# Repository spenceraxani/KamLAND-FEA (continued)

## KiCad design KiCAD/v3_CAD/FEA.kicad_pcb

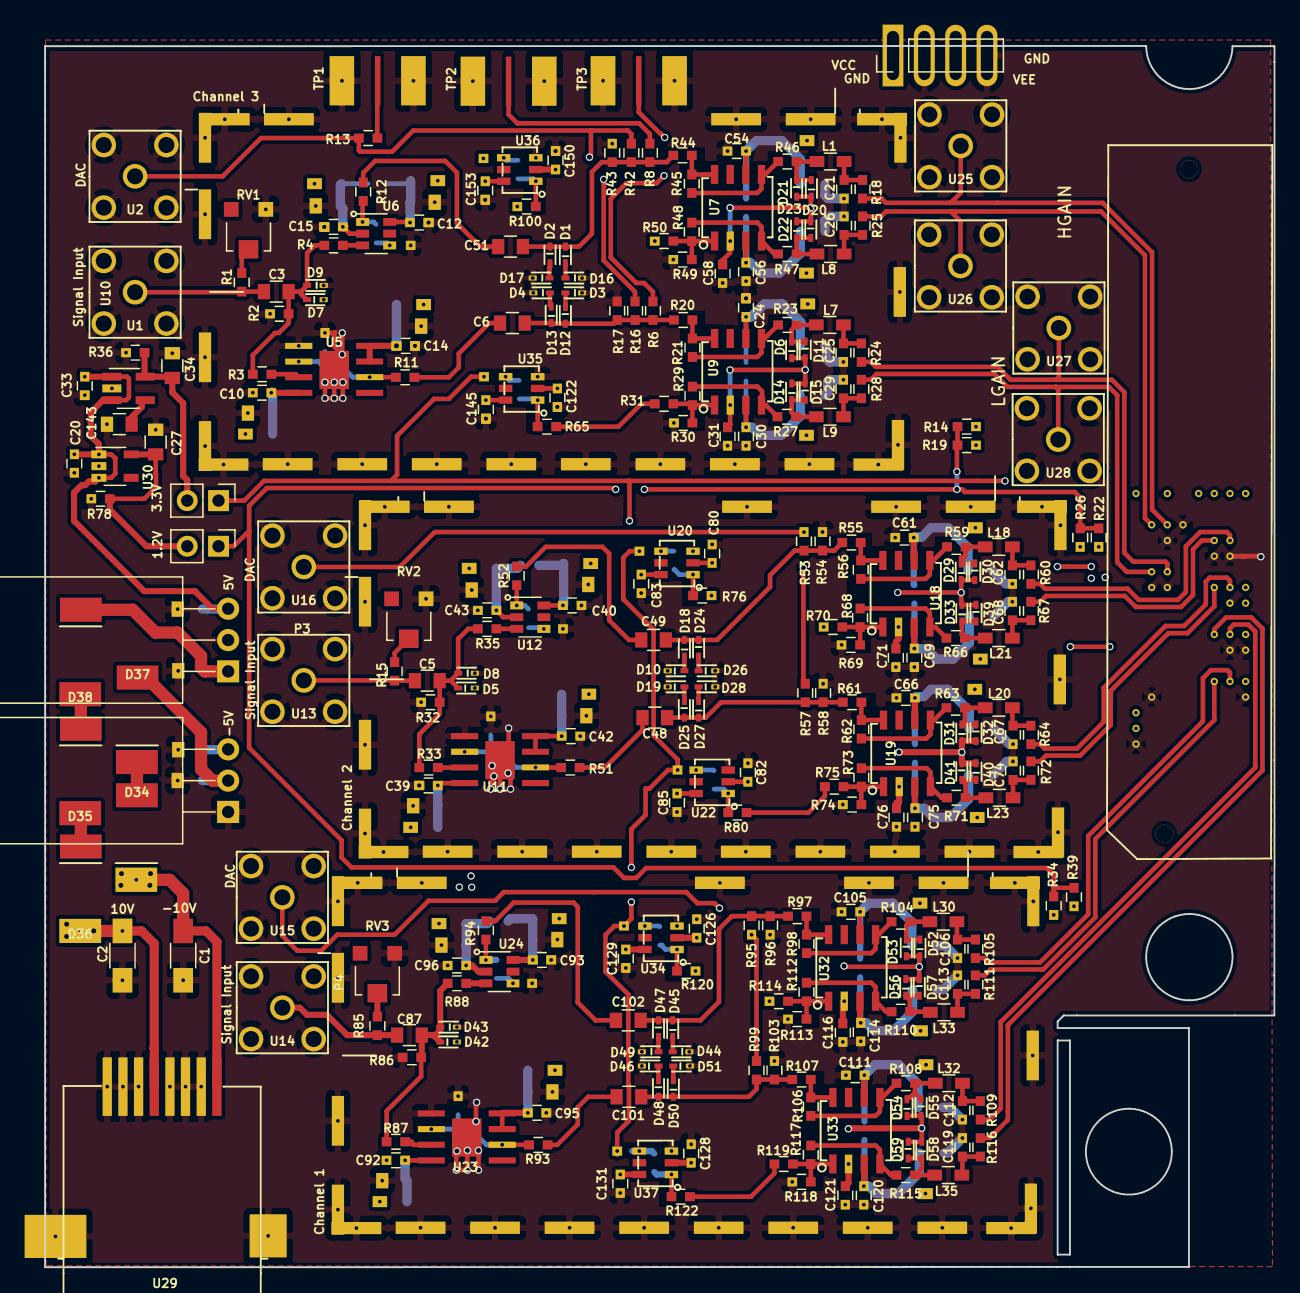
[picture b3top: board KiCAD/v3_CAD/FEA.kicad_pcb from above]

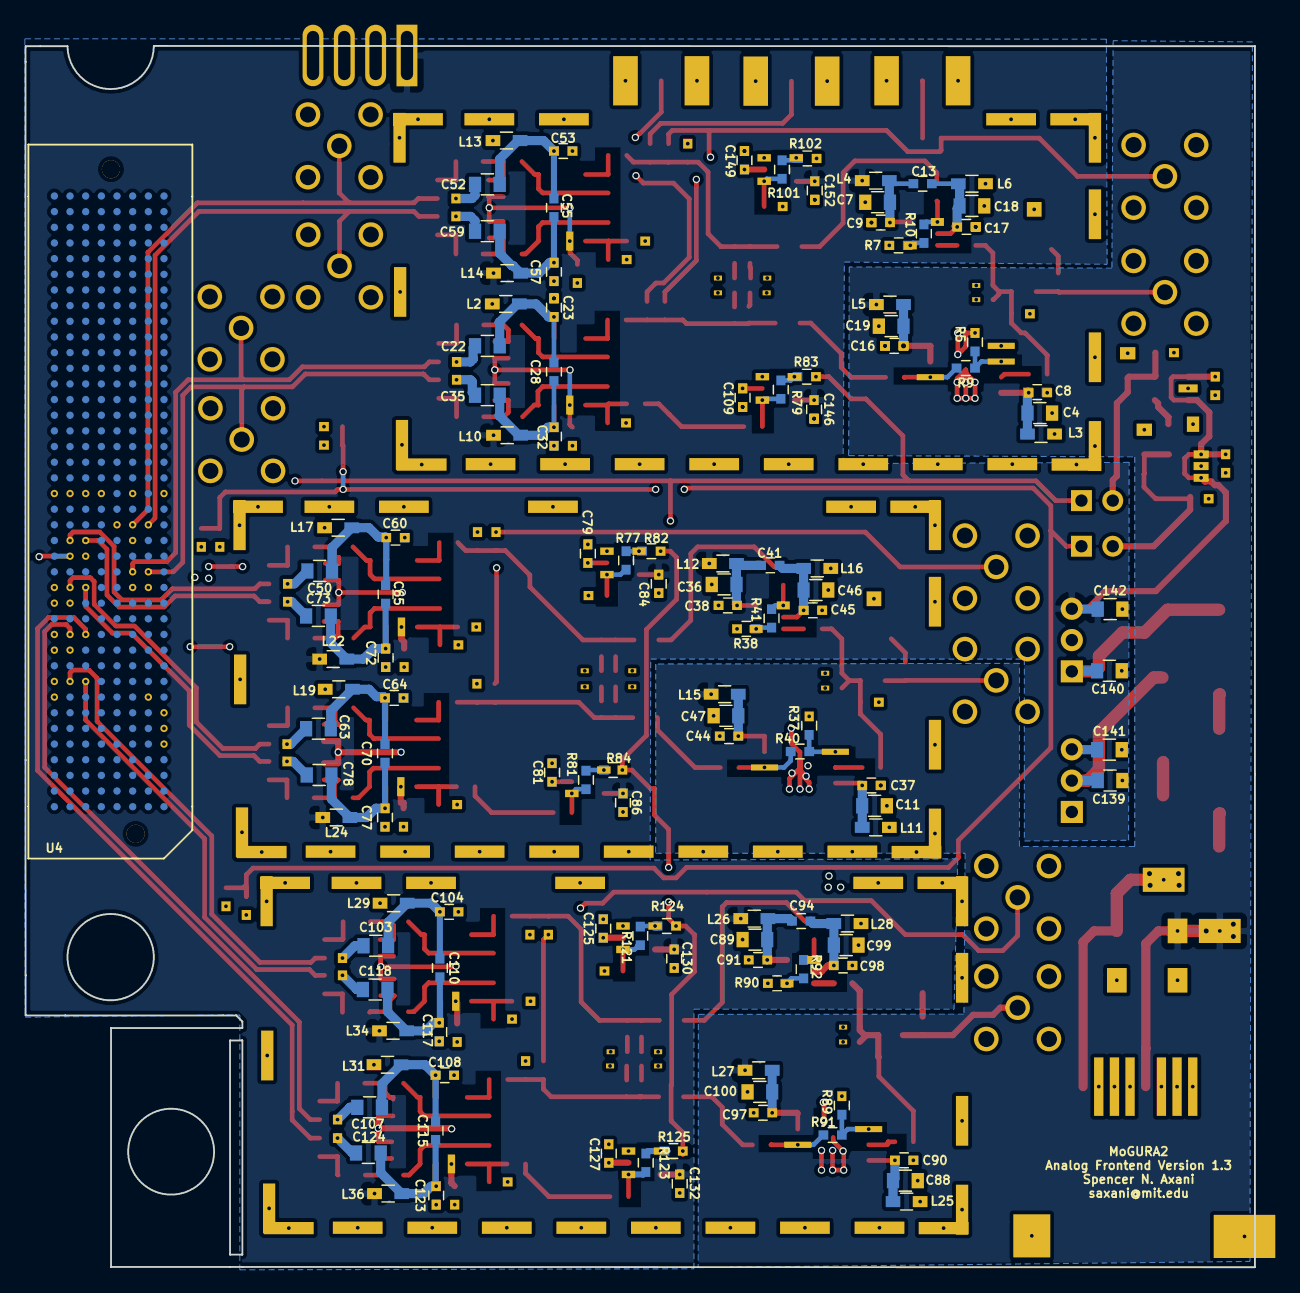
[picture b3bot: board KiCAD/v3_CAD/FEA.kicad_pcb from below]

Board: 4 copper layers, 99.7 x 99.1 mm, 409 parts (122 on the bottom side), 180 nets.

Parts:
C1, C2: CP1; C_1206_HandSoldering
C3, C5, C87: 0; C_0805
C4, C7, C11, C18, C19, C22, C35, C36, C46, C47, C50, C52, C59, C63, C73, C78, C88, C89, C99, C100, C103, C107, C118, C124: 10uF; C_0805
C6, C48, C49, C51, C101, C102: 22u; C_0805
C8, C9, C13, C16, C17, C21, C23, C25, C26, C28, C29, C31, C32, C37, C38, C41, C44, C45, C53, C55, C57, C58, C60, C62, C64, C65, C67, C68, C70, C71, C72, C74, C76, C77, C79, C81, C84, C86, C90, C91, C94, C97, C98, C104, C106, C108, C109, C110, C112, C113, C115, C116, C117, C119, C121, C123, C125, C127, C130, C132, C146, C149, C153: 0.1uF; C_0603
C10, C14, C39, C42, C92, C95: 100pF; C_0603
C12, C15, C24, C30, C40, C43, C54, C56, C61, C66, C69, C75, C80, C82, C83, C85, C93, C96, C105, C111, C114, C120, C122, C126, C128, C129, C131, C145, C150, C152: 10nF; C_0603
C20, C33: 1uF; C_0603
C27: 1u; C_0805
C34: 2.2u; C_0805
C139: 0.47u; C_0805
C140: 0.33uF; C_0805
C141: 2.2uF; C_0805
C142: 0.1uF; C_0805
C143: 1uF; C_0805
D1, D2, D3, D4, D5, D6, D7, D8, D9, D10, D11, D12, D13, D14, D15, D16, D17, D18, D19, D20, D21, D22, D23, D24, D25, D26, D27, D28, D29, D30, D31, D32, D33, D39, D40, D41, D42, D43, D44, D45, D46, D47, D48, D49, D50, D51, D52, D53, D54, D55, D56, D57, D58, D59: D; RB751
D34, D35, D36, D37, D38: D; SA3-Diode
JP8, JP10: Jumper_NC_Small; Pin_Header_Straight_1x02_Pitch2.54mm
L1, L2, L3, L4, L5, L6, L7, L8, L9, L10, L11, L12, L13, L14, L15, L16, L17, L18, L19, L20, L21, L22, L23, L24, L25, L26, L27, L28, L29, L30, L31, L32, L33, L34, L35, L36: BLM18BB221SN1; R_0603_HandSoldering
P1: CONN_01X04; Pin_Header_Straight_1x04_Pitch2.54mm
P2, P3, P4: CONN_01X01; RF SHIELD 1.094 X 2.23 SMD
R1, R15, R85: 100k; C_0603
R2, R3, R4, R12, R32, R33, R35, R52, R65, R76, R80, R86, R87, R88, R94, R100, R120, R122: 49.9; C_0603
R5, R9, R37, R40, R89, R91: 2.1k; C_0603
R6, R8, R13, R14, R19, R22, R26, R34, R39: R; C_0603
R7, R38, R90: 100; C_0603
R10, R41, R92: 390; C_0603
R11, R21, R29, R45, R48, R51, R56, R62, R68, R73, R93, R98, R107, R112, R117: 200; C_0603
R16, R17, R42, R43, R53, R54, R57, R58, R95, R96, R99, R103: 500; C_0603
R18, R23, R24, R25, R27, R28, R46, R47, R59, R60, R63, R64, R66, R67, R71, R72, R104, R105, R108, R109, R110, R111, R115, R116: 40; C_0603
R20, R44, R55, R61, R97, R106: 120; C_0603
R30, R49, R69, R74, R113, R118: 170; C_0603
R31, R50, R70, R75, R114, R119: 1.5k; C_0603
R36, R78: 10k; C_0603
R77, R79, R81, R82, R83, R84, R101, R102, R121, R123, R124, R125: 560; C_0603
RV1, RV2, RV3: POT; Potentiometer_Trimmer-EVM3E
U1, U2, U13, U14, U15, U16, U25, U26, U27, U28: SMA; SMA_90
U3, U8, U31: SMA; SMA_side_mount
U4: LPAM
U5, U11, U23: THS3491; THS3491_HSOIC
U6, U12, U24: LMH6703; SOT-23-6
U7, U9, U18, U19, U32, U33: LMH6552; LMH6550
U10: TPS7993; SOT-23-5_HandSoldering
U17: UA7905CKCSE3_-5V; TO-220_Horizontal
U20, U22, U34, U35, U36, U37: LMH6702MF; LMH6702
U21: L78S_5V; TO-220_Horizontal
U29: Ethernet; Ethernet_90_8P8C
U30: 5-Lead_TSOT; TSOT-23-5

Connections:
1.2V: JP10.1, R14.1, R19.1, R22.1, R26.1, R34.1, R39.1
5V: C20.1, C33.1, C83.2, C84.2, C85.2, C86.2, C129.2, C130.2, C131.2, C132.2, C142.1, C145.2, C146.2, C152.2, C153.2, L4.2, L10.1, L12.2, L14.1, L22.1, L24.1, L26.2, L34.1, L36.1, P1.1, U10.1, U10.3, U20.6, U21.3, U22.6, U30.1, U30.3, U34.6, U35.6, U36.6, U37.6
10V: C2.2, D36.2, L5.2, L15.2, L27.2, U29.4
-5V: C79.2, C80.2, C81.2, C82.2, C109.2, C122.2, C125.2, C126.2, C127.2, C128.2, C141.1, C149.2, C150.2, L2.2, L6.1, L13.2, L16.1, L17.2, L19.2, L28.1, L29.2, L31.2, P1.3, U17.3, U20.2, U22.2, U34.2, U35.2, U36.2, U37.2
-10V: C1.1, D5.2, D7.2, D34.1, D42.2, L3.1, L11.1, L25.1, U29.8
/Amp1/DAC_input: R13.1, R16.1, R42.1, U2.1
/Amp1/HGain_Bias: R50.2, R100.1
/Amp1/LGain_Bias: R31.2, R65.2
/Amp1/Sig_in: C3.2, R1.1, U1.1
/Amp1/TP2: C51.2, D1.2, D2.1, R8.1, R42.2, R43.1, R44.2
/Amp1/TP3: C6.2, D12.2, D13.1, R6.1, R16.2, R17.1, R20.2
/sheet605AA4D2/DAC_input: R53.1, R57.1, U16.1
/sheet605AA4D2/HGain_Bias: R70.2, R76.1
/sheet605AA4D2/LGain_Bias: R75.2, R80.2
/sheet605AA4D2/Sig_in: C5.2, R15.1, U13.1
/sheet605AA4D2/TP2: C49.2, D18.2, D24.1, R53.2, R54.1, R55.2
/sheet605AA4D2/TP3: C48.2, D25.2, D27.1, R57.2, R58.1, R61.2
/sheet60926C69/DAC_input: R95.1, R99.1, U15.1
/sheet60926C69/HGain_Bias: R114.2, R120.1
/sheet60926C69/LGain_Bias: R119.2, R122.2
/sheet60926C69/Sig_in: C87.2, R85.1, U14.1
/sheet60926C69/TP2: C102.2, D45.2, D47.1, R95.2, R96.1, R97.2
/sheet60926C69/TP3: C101.2, D48.2, D50.1, R99.2, R103.1, R106.2
Earth: C1.2, C2.1, C4.1, C7.1, C8.1, C9.1, C10.1, C11.1, C12.1, C14.1, C15.1, C16.1, C17.1, C18.1, C19.1, C20.2, C21.2, C22.1, C23.1, C24.1, C25.2, C26.2, C27.2, C29.2, C30.1, C31.2, C32.1, C33.2, C34.2, C35.1, C36.1, C37.1, C38.1, C39.1, C40.1, C42.1, C43.1, C44.1, C45.1, C46.1, C47.1, C50.1, C52.1, C53.1, C54.1, C56.1, C57.1, C58.2, C59.1, C60.1, C61.1, C62.2, C63.1, C64.1, C66.1, C67.2, C68.2, C69.1, C71.2, C72.1, C73.1, C74.2, C75.1, C76.2, C77.1, C78.1, C79.1, C80.1, C81.1, C82.1, C83.1, C84.1, C85.1, C86.1, C88.1, C89.1, C90.1, C91.1, C92.1, C93.1, C95.1, C96.1, C97.1, C98.1, C99.1, C100.1, C103.1, C104.1, C105.1, C106.2, C107.1, C108.1, C109.1, C111.1, C112.2, C113.2, C114.1, C116.2, C117.1, C118.1, C119.2, C120.1, C121.2, C122.1, C123.1, C124.1, C125.1, C126.1, C127.1, C128.1, C129.1, C130.1, C131.1, C132.1, C139.2, C140.2, C141.2, C142.2, C143.2, C145.1, C146.1, C149.1, C150.1, C152.1, C153.1, D3.1, D4.2, D8.1, D9.1, D10.1, D16.1, D17.2, D19.1, D26.2, D28.2, D43.1, D44.1, D46.1, D49.2, D51.2, P1.2, P1.4, P2.1, P3.1, P4.1, R2.1, R5.2, R7.1, R17.2, R30.2, R32.1, R36.1, R37.2, R38.1, R43.2, R49.2, R54.2, R58.2, R69.2, R74.2, R78.1, R86.1, R89.2, R90.1, R96.2, R103.2, R113.2, R118.2, RV1.1, RV2.1, RV3.1, U1.2, U2.2, U3.2, U4.A5, U4.B8, U4.B15, U4.C15, U4.C18, U4.D19, U4.F17, U4.G11, U4.G14, U4.G17, U4.H8, U4.H11, U4.H17, U5.1, U5.9, U8.2, U10.2, U11.1, U11.9, U13.2, U14.2, U15.2, U16.2, U17.1, U20.3, U21.2, U22.3, U23.1, U23.9, U25.2, U26.2, U27.2, U28.2, U29.0, U29.1, U29.2, U29.3, U29.5, U29.6, U29.7, U30.2, U31.2, U34.3, U35.3, U36.3, U37.3
LevelShift_V: JP8.1, R82.1, R83.2, R84.2, R102.1, R124.1, R125.2, U4.A7
unnamed: C3.1, D7.1, D9.2, R2.2, R3.1, R4.2
unnamed: C5.1, D5.1, D8.2, R32.2, R33.1, R35.2
unnamed: C6.1, R11.1
unnamed: C4.2, C8.2, C10.2, L3.2, U5.4
unnamed: C11.2, C37.2, C39.2, L11.2, U11.4
unnamed: C7.2, C9.2, C12.2, C13.2, L4.1, U6.6
unnamed: C13.1, C15.2, C17.2, C18.2, L6.2, U6.2
unnamed: C14.2, C16.2, C19.2, L5.1, U5.7, U5.8
unnamed: C21.1, L1.1, R18.2
unnamed: C22.2, C23.2, C24.2, C28.2, L2.1, U9.6
unnamed: C25.1, L7.1, R24.2
unnamed: C26.1, L8.2, R25.2
unnamed: C27.1, JP10.2, R78.2, U30.5
unnamed: C28.1, C30.2, C32.2, C35.2, L10.2, U9.3
unnamed: C29.1, L9.2, R28.2
unnamed: C34.1, JP8.2, R36.2, U10.5
unnamed: C36.2, C38.2, C40.2, C41.2, L12.1, U12.6
unnamed: C41.1, C43.2, C45.2, C46.2, L16.2, U12.2
unnamed: C42.2, C44.2, C47.2, L15.1, U11.7, U11.8
unnamed: C48.1, R51.1
unnamed: C49.1, R52.1
unnamed: C50.2, C60.2, C61.2, C65.2, L17.1, U18.6
unnamed: C51.1, R12.1
unnamed: C52.2, C53.2, C54.2, C55.2, L13.1, U7.6
unnamed: C55.1, C56.2, C57.2, C59.2, L14.2, U7.3
unnamed: C62.1, L18.1, R60.2
unnamed: C63.2, C64.2, C66.2, C70.2, L19.1, U19.6
unnamed: C65.1, C69.2, C72.2, C73.2, L22.2, U18.3
unnamed: C67.1, L20.1, R64.2
unnamed: C68.1, L21.2, R67.2
unnamed: C70.1, C75.2, C77.2, C78.2, L24.2, U19.3
unnamed: C74.1, L23.2, R72.2
unnamed: C87.1, D42.1, D43.2, R86.2, R87.1, R88.2
unnamed: C88.2, C90.2, C92.2, L25.2, U23.4
unnamed: C89.2, C91.2, C93.2, C94.2, L26.1, U24.6
unnamed: C94.1, C96.2, C98.2, C99.2, L28.2, U24.2
unnamed: C95.2, C97.2, C100.2, L27.1, U23.7, U23.8
unnamed: C101.1, R93.1
unnamed: C102.1, R94.1
unnamed: C103.2, C104.2, C105.2, C110.2, L29.1, U32.6
unnamed: C106.1, L30.1, R105.2
unnamed: C107.2, C108.2, C111.2, C115.2, L31.1, U33.6
unnamed: C110.1, C114.2, C117.2, C118.2, L34.2, U32.3
unnamed: C112.1, L32.1, R109.2
unnamed: C113.1, L33.2, R111.2
unnamed: C115.1, C120.2, C123.2, C124.2, L36.2, U33.3
unnamed: C119.1, L35.2, R116.2
unnamed: C139.1, D37.2, U17.2
unnamed: C140.1, D38.1, U21.1
unnamed: C143.1, U10.4
unnamed: D1.1, D16.2
unnamed: D10.2, D18.1
unnamed: D6.2, D11.1, L7.2, R23.1
unnamed: D3.2, D12.1
unnamed: D4.1, D13.2
unnamed: D14.1, D15.2, L9.1, R27.1
unnamed: D2.2, D17.1
unnamed: D19.2, D25.1
unnamed: D20.2, D21.1, L1.2, R46.1
unnamed: D22.1, D23.2, L8.1, R47.1
unnamed: D24.2, D26.1
unnamed: D27.2, D28.1
unnamed: D29.2, D30.1, L18.2, R59.1
unnamed: D31.2, D32.1, L20.2, R63.1
unnamed: D33.1, D39.2, L21.1, R66.1
unnamed: D34.2, D37.1
unnamed: D35.1, D38.2
unnamed: D35.2, D36.1
unnamed: D40.1, D41.2, L23.1, R71.1
unnamed: D44.2, D45.1
unnamed: D46.2, D48.1
unnamed: D47.2, D49.1
unnamed: D50.2, D51.1
unnamed: D52.2, D53.1, L30.2, R104.1
unnamed: D54.2, D55.1, L32.2, R108.1
unnamed: D56.1, D57.2, L33.1, R110.1
unnamed: D58.1, D59.2, L35.1, R115.1
unnamed: R1.2, RV1.2
unnamed: R3.2, U5.3
unnamed: R4.1, U6.3
unnamed: R5.1, R9.2, U5.2
unnamed: R6.2, U31.1
unnamed: R8.2, U3.1
unnamed: R10.1, R12.2, U6.1
unnamed: R7.2, R10.2, U6.4
unnamed: R9.1, R11.2, U5.6
unnamed: R13.2, U8.1
unnamed: R15.2, RV2.2
unnamed: R20.1, R21.2, U9.8
unnamed: R21.1, R23.2, U9.5
unnamed: R27.2, R29.2, U9.4
unnamed: R29.1, R30.1, R31.1, U9.1
unnamed: R33.2, U11.3
unnamed: R35.1, U12.3
unnamed: R37.1, R40.2, U11.2
unnamed: R38.2, R41.2, U12.4
unnamed: R40.1, R51.2, U11.6
unnamed: R41.1, R52.2, U12.1
unnamed: R44.1, R45.2, U7.8
unnamed: R45.1, R46.2, U7.5
unnamed: R47.2, R48.2, U7.4
unnamed: R48.1, R49.1, R50.1, U7.1
unnamed: R55.1, R56.2, U18.8
unnamed: R56.1, R59.2, U18.5
unnamed: R61.1, R62.2, U19.8
unnamed: R62.1, R63.2, U19.5
unnamed: R65.1, R79.2, U35.1
unnamed: R66.2, R68.2, U18.4
unnamed: R68.1, R69.1, R70.1, U18.1
unnamed: R71.2, R73.2, U19.4
unnamed: R73.1, R74.1, R75.1, U19.1
unnamed: R76.2, R77.1, U20.1
unnamed: R77.2, R82.2, U20.4
unnamed: R79.1, R83.1, U35.4
unnamed: R80.1, R81.2, U22.1
unnamed: R81.1, R84.1, U22.4
unnamed: R85.2, RV3.2
unnamed: R87.2, U23.3
unnamed: R88.1, U24.3
unnamed: R89.1, R91.2, U23.2
unnamed: R90.2, R92.2, U24.4
unnamed: R91.1, R93.2, U23.6
unnamed: R92.1, R94.2, U24.1
unnamed: R97.1, R98.2, U32.8
unnamed: R100.2, R101.1, U36.1
unnamed: R101.2, R102.2, U36.4
unnamed: R98.1, R104.2, U32.5
unnamed: R106.1, R107.2, U33.8
unnamed: R107.1, R108.2, U33.5
unnamed: R110.2, R112.2, U32.4
unnamed: R112.1, R113.1, R114.1, U32.1
unnamed: R115.2, R117.2, U33.4
unnamed: R117.1, R118.1, R119.1, U33.1
unnamed: R120.2, R121.1, U34.1
unnamed: R121.2, R124.2, U34.4
unnamed: R122.1, R123.2, U37.1
unnamed: R123.1, R125.1, U37.4
RFMC_ADC_00_N: R111.1, U4.F9
RFMC_ADC_00_P: R105.1, U4.G9
RFMC_ADC_02_N: R116.1, U4.F12
RFMC_ADC_02_P: R109.1, U4.G12
RFMC_ADC_04_N: R72.1, U4.F15
RFMC_ADC_04_P: R64.1, U4.G15
RFMC_ADC_05_N: R28.1, U4.B16, U28.1
RFMC_ADC_05_P: R24.1, U4.C16, U27.1
RFMC_ADC_06_N: R67.1, U4.F18
RFMC_ADC_06_P: R60.1, U4.G18
RFMC_ADC_07_N: R25.1, U4.B19, U26.1
RFMC_ADC_07_P: R18.1, U4.C19, U25.1
VCM01_224: C116.1, D52.1, D53.2, D56.2, D57.1, R34.2, U4.A21, U32.2
VCM01_225: C121.1, D54.1, D55.2, D58.2, D59.1, R39.2, U4.C21, U33.2
VCM01_226: C76.1, D31.1, D32.2, D40.2, D41.1, R26.2, U4.E21, U19.2
VCM01_227: C71.1, D29.1, D30.2, D33.2, D39.1, R22.2, U4.G21, U18.2
VCM23_226: C31.1, D6.1, D11.2, D14.2, D15.1, R19.2, U4.F21, U9.2
VCM23_227: C58.1, D20.1, D21.2, D22.2, D23.1, R14.2, U4.H21, U7.2

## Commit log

2020-06-12 adding files
2020-09-14 adding doc
2021-04-20 Adding expansion board documentation
2021-04-20 v3 stuff
